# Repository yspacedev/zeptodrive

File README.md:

Constant current buck-boost converter based on the TPS63070 and INA180. The TPS63070 is a constant voltage buck-boost converter, so I'm using an INA180 (similar to this app note: https://www.ti.com/lit/an/slva419d/slva419d.pdf?ts=1689743420901) to convert it to a constant current converter.

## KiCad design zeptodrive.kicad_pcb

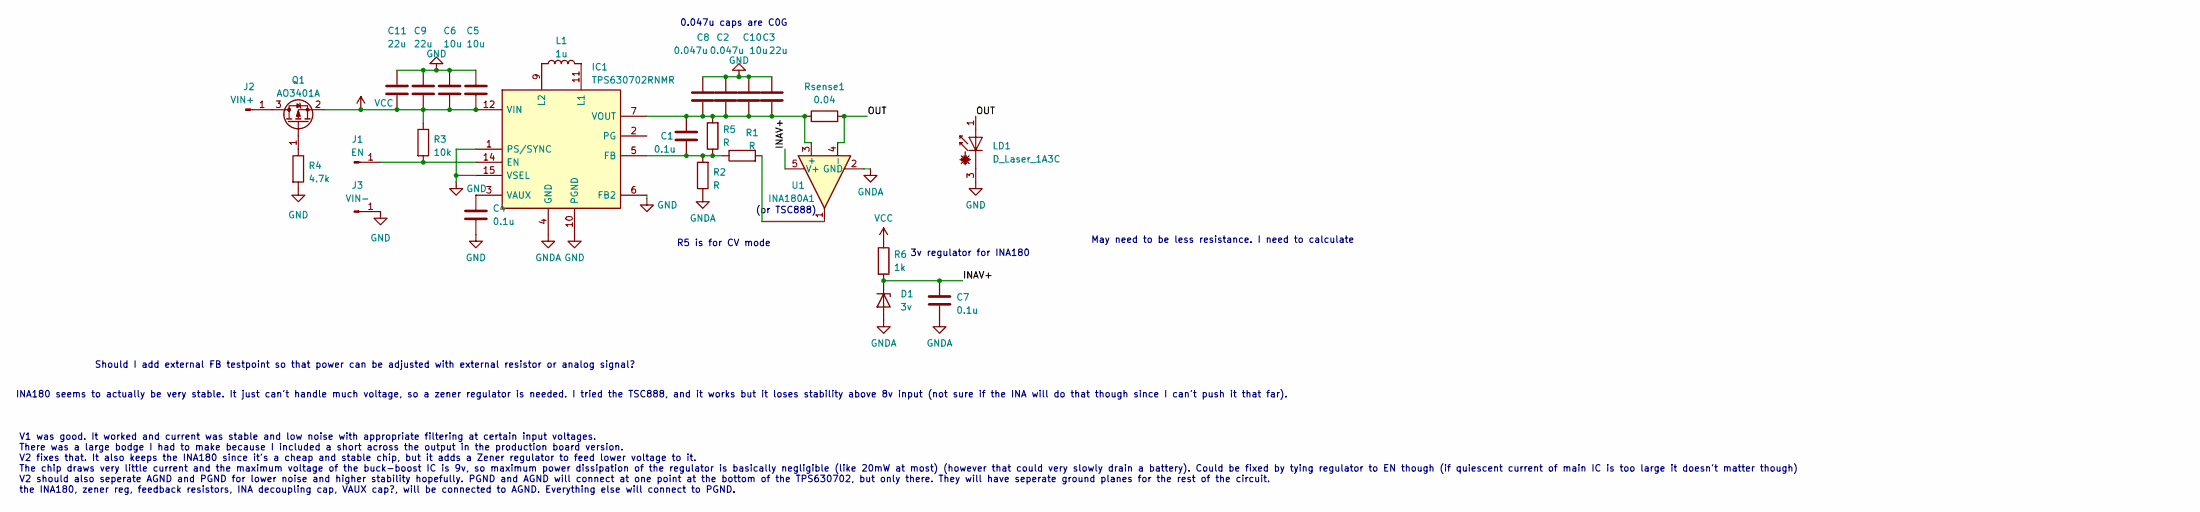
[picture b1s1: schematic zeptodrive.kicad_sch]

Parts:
C1, C4: 0.1u; C_0603_1608Metric
C2, C8: 0.047u; C_0805_2012Metric
C3, C9, C11: 22u; C_0805_2012Metric
C5, C6, C10: 10u; C_0805_2012Metric
C7: 0.1u; C_0402_1005Metric
D1: 3v; D_SOD-523
IC1: TPS630702RNMR; TPS630701RNMR; Mouser Part Number 595-TPS630702RNMR
J1: EN; TestPoint_Pad_D1.5mm
J2: VIN+; Small circular hole connector
J3: VIN-; Small circular hole connector
L1: 1u; L_1008_2520Metric
LD1: D_Laser_1A3C; Laser Diode Side Mount 1 side 2 pin
Q1: AO3401A; SOT-23
R1, R5: R; R_0603_1608Metric
R2: R; R_0805_2012Metric
R3: 10k; R_0603_1608Metric
R4: 4.7k; R_0603_1608Metric
R6: 1k; R_0402_1005Metric
Rsense1: 0.04; R_1206_3216Metric
U1: INA180A1; SOT-23-5

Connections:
/INAV+: C7.1, D1.1 (K), R6.2, U1.5 (V+)
/OUT: LD1.1 (A), Rsense1.2, U1.4 (-)
GND: C2.1, C3.1, C4.2, C5.1, C6.1, C8.1, C9.1, C10.1, C11.1, IC1.1 (PS/SYNC), IC1.6 (FB2), IC1.10 (PGND), IC1.15 (VSEL), J3.1, LD1.3 (K), R4.2
GNDA: C7.2, D1.2 (A), IC1.4 (GND), R2.1, U1.2 (GND)
unnamed: IC1.14 (EN), J1.1, R3.2
unnamed: C1.2, IC1.5 (FB), R1.1, R2.2, R5.1
unnamed: IC1.11 (L1), L1.2
unnamed: IC1.9 (L2), L1.1
unnamed: C4.1, IC1.3 (VAUX)
unnamed: J2.1, Q1.3 (D)
unnamed: Q1.1 (G), R4.1
unnamed: R1.2, U1.1
unnamed: C1.1, C2.2, C3.2, C8.2, C10.2, IC1.7 (VOUT), IC1.8 (VOUT), R5.2, Rsense1.1, U1.3 (+)
VCC: C5.2, C6.2, C9.2, C11.2, IC1.12 (VIN), IC1.13 (VIN), Q1.2 (S), R3.1, R6.1

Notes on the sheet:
V1 was good. It worked and current was stable and low noise with appropriate filtering at certain input voltages. There was a large bodge I had to make because I included a short across the output in the production board version. V2 fixes that. It also keeps the INA180 since it's a cheap and stable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
Should I add external FB testpoint so that power can be adjusted with external resistor or analog signal?
3v regulator for INA180
INA180 seems to actually be very stable. It just can't handle much voltage, so a zener regulator is needed. I tried the TSC888, and it works but it loses stability above 8v input (not sure if the INA will do that though since I can't push it that far).
(or TSC888)
May need to be less resistance. I need to calculate
R5 is for CV mode
0.047u caps are C0G

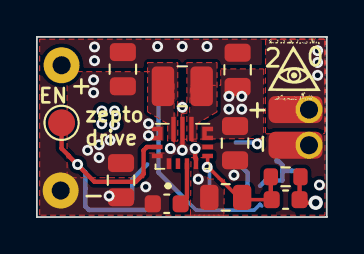
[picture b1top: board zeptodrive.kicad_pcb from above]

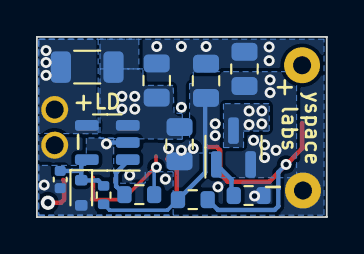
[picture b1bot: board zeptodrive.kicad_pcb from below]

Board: 4 copper layers, 16.1 x 10.0 mm, 27 parts (13 on the bottom side), 14 nets.
